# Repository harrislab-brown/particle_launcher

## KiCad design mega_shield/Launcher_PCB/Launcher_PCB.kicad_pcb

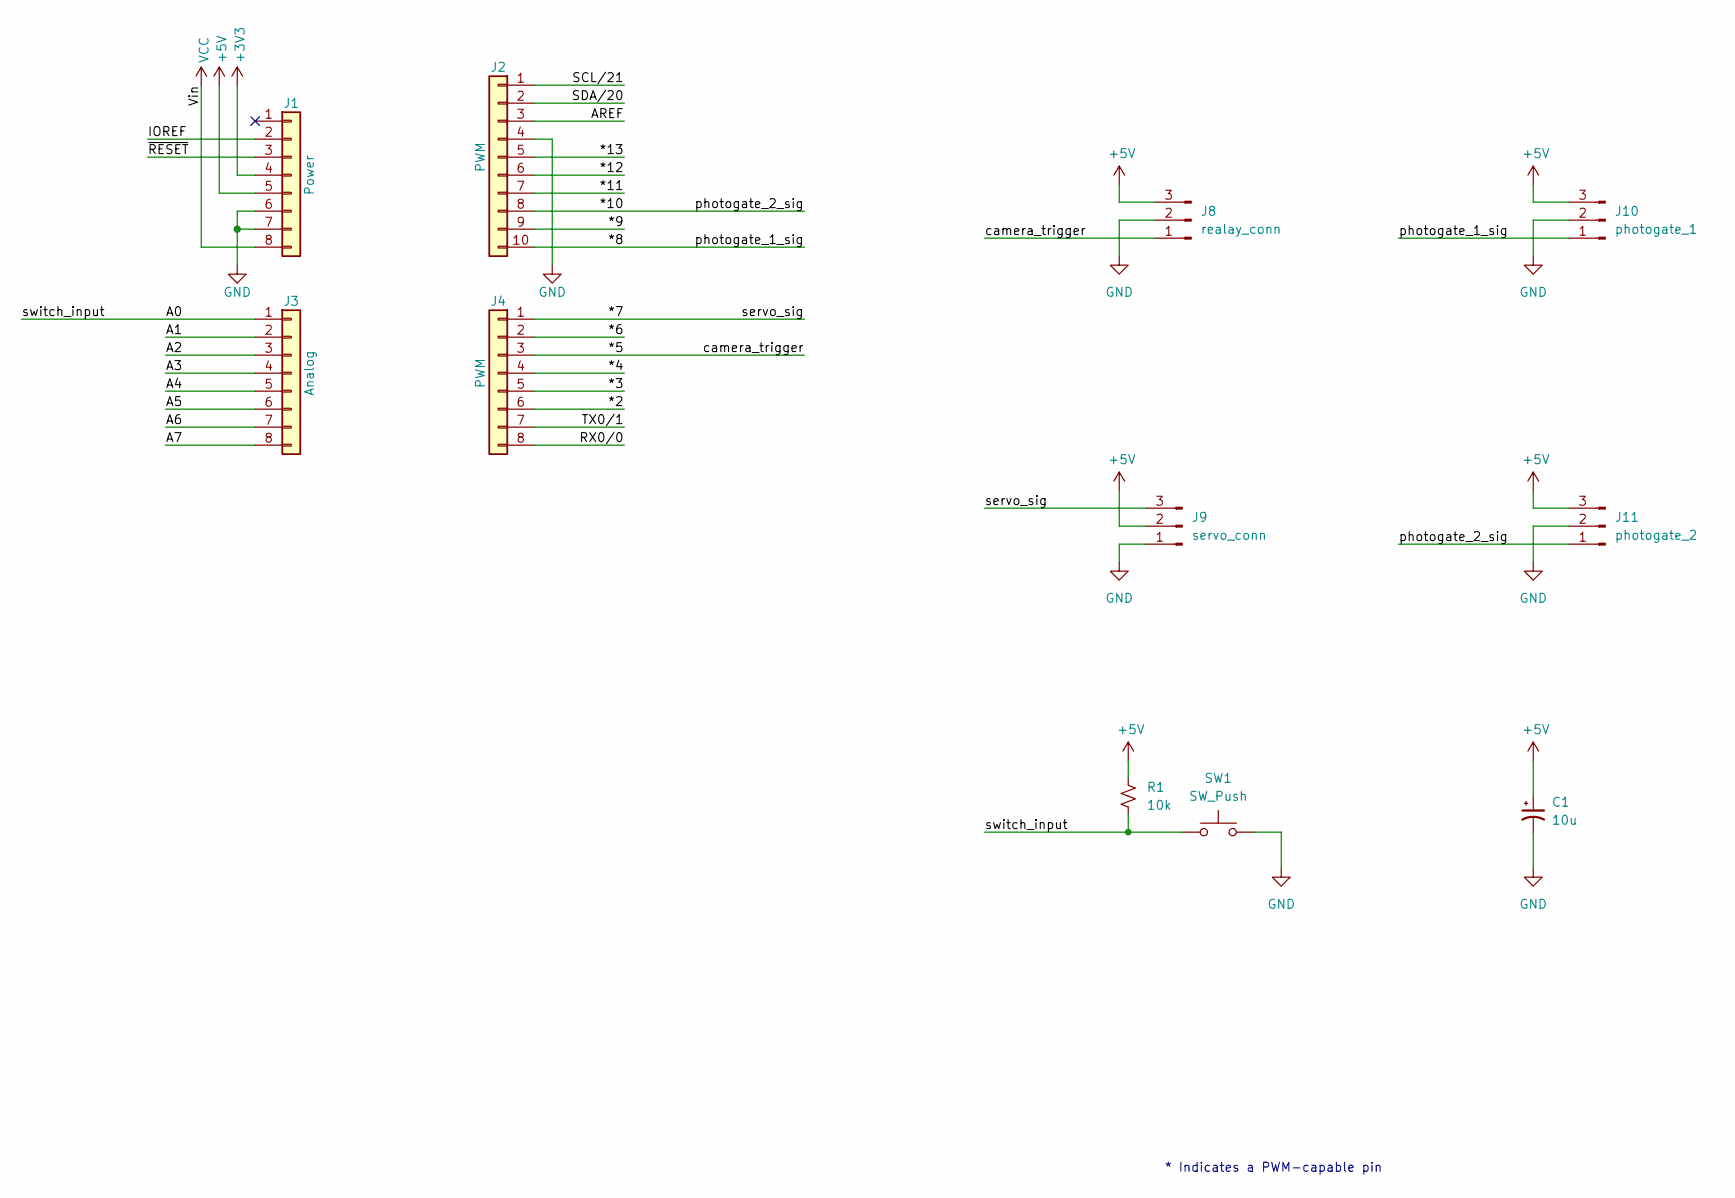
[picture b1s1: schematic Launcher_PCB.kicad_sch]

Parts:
C1: 10u; CP_Elec_5x5.4
J1: Power; PinHeader_1x08_P2.54mm_Vertical
J2: PWM; PinSocket_1x10_P2.54mm_Vertical
J3: Analog; PinSocket_1x08_P2.54mm_Vertical
J4: PWM; PinSocket_1x08_P2.54mm_Vertical
J8: realay_conn; PinHeader_1x03_P2.54mm_Vertical_SMD_Pin1Left
J9: servo_conn; PinHeader_1x03_P2.54mm_Vertical_SMD_Pin1Left
J10: photogate_1; PinHeader_1x03_P2.54mm_Vertical_SMD_Pin1Left
J11: photogate_2; PinHeader_1x03_P2.54mm_Vertical_SMD_Pin1Left
R1: 10k; R_0603_1608Metric_Pad0.98x0.95mm_HandSolder
SW1: SW_Push; SW_PUSH_6mm

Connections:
+3V3: J1.4
+5V: C1.1, J1.5, J8.3, J9.2, J10.3, J11.3, R1.1
/*2: J4.6
/*3: J4.5
/*4: J4.4
/*5: J4.3, J8.1
/*6: J4.2
/*7: J4.1, J9.3
/*8: J2.10, J10.1
/*9: J2.9
/*10: J2.8, J11.1
/*11: J2.7
/*12: J2.6
/*13: J2.5
/A0: J3.1, R1.2, SW1.1
/A1: J3.2
/A2: J3.3
/A3: J3.4
/A4: J3.5
/A5: J3.6
/A6: J3.7
/A7: J3.8
/AREF: J2.3
/IOREF: J1.2
/RX0/0: J4.8
/SCL/21: J2.1
/SDA/20: J2.2
/TX0/1: J4.7
/~RESET: J1.3
GND: C1.2, J1.6, J1.7, J2.4, J8.2, J9.1, J10.2, J11.2, SW1.2
VCC: J1.8

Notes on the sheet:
* Indicates a PWM-capable pin

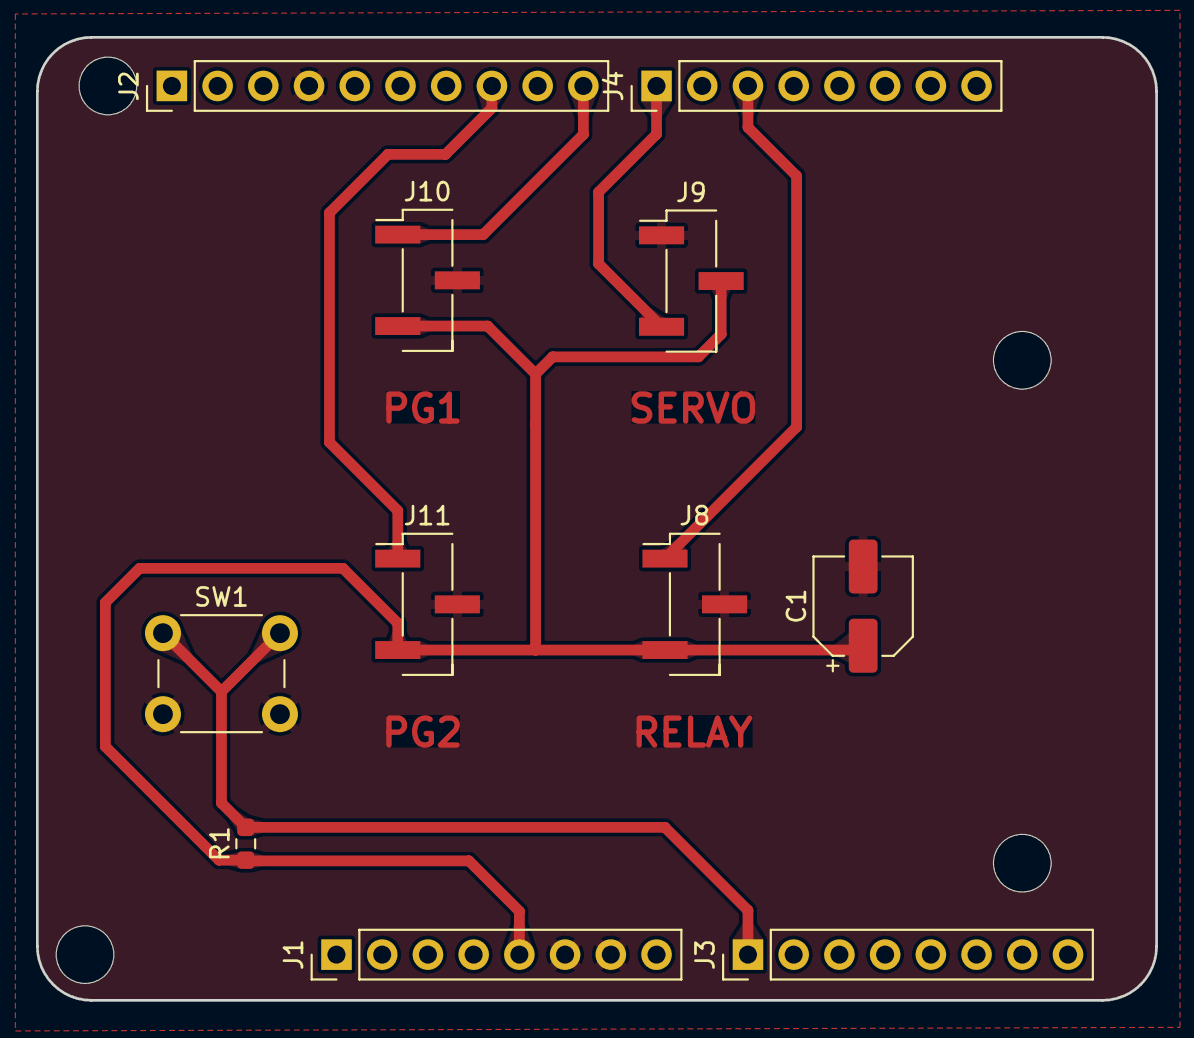
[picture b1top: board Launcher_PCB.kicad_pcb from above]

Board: 2 copper layers, 62.2 x 53.5 mm, 15 parts (0 on the bottom side), 7 nets.

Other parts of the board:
MH1, MH2, MH3, MH4: MountingHole_3.2mm

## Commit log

2025-12-12 wiring and pinout tested
2026-03-05 designed an arduino hat to control particle launcher
2026-03-10 basic code for milled PCB is working. Switched to arduino uno
2026-03-11 Changed camera delay and servo release angles based on what worked in our meeting on 3/11/26. This is the current code running on the arduino servo release
2026-03-11 Added MATLAB image processing scripts for tracking particle
2026-03-23 calibrated servo and relay timing in arduino script, along with some other small changes. adjusted matlab sphere tracking to eliminate need to crop mirrored video. tested with sample mirrored video t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
2026-03-24 adjustments to matlab sphere tracking to make data collection easier, quicker. bug fixes.
2026-03-26 bug fixes. changed sphere tracking such that user need only perform the initial 3 calibration steps for the first video of a group of many taken from the exact same angle. also, user only needs to se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
2026-04-06 apr62026
2026-04-15 before thesis first draft submission
2026-04-15 added CAD folder
2026-04-15 added CAD folder take 2
2026-04-17 moved some files around
2026-04-17 added fusion and solidworks CAD files, drawings, 3D print files, laser cut files for Version 6
2026-04-17 added CAD files for previous versions and for various 3D-printed jigs
2026-04-17 folder resturcture
2026-04-17 folder restructure
2026-05-04 post thesis presentation commit
2026-05-19 added CAD files for 1mm launcher variant
2026-05-19 added 3mf print file for 1mm variant
2026-05-19 added Thesis document and presentation slides for reference
